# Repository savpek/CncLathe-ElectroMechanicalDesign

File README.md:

CncLathe-ElectroMechanicalDesign
================================

Cnc lathe electro and mechanical design.

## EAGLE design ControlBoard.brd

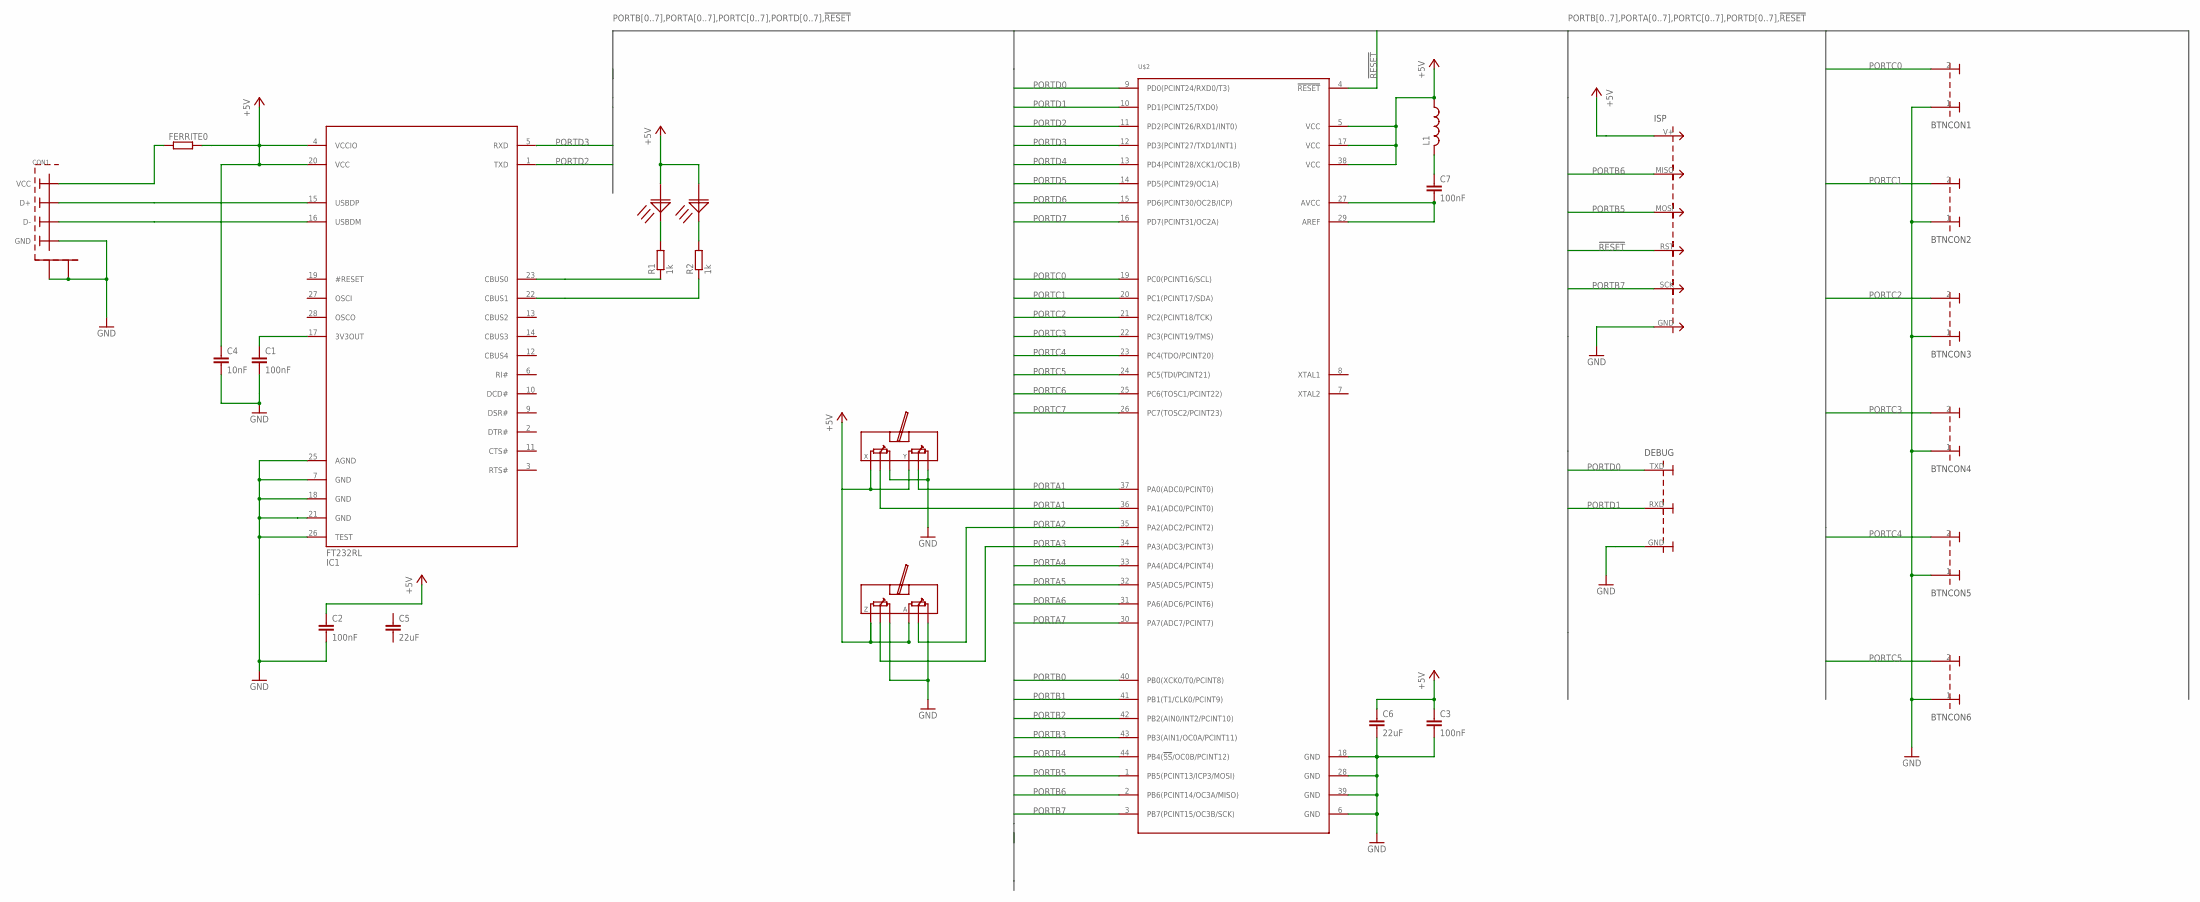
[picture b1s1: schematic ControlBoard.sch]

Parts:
BTNCON1, BTNCON2, BTNCON3, BTNCON4, BTNCON5, BTNCON6: CONNECTOR_2PIN1X2_WIRE; 1X2_WIRE
C1, C2, C3, C7: 100nF; C0805@1; MPN KP-2012SEC
C4: 10nF; C0805@1; MPN 04023D103KAT2A
C5, C6: 22uF; C1206
CON1: USB-BWUERTH-ELECTRONIC-USB-B; USB-B-THROUGH-HOLE
DEBUG: CONNECTOR_3PINUSART; 1X3_USART
FERRITE0: R-EU_R0805; R0805
IC1: FT232RL; SSOP28
ISP: CONNECTOR_6PIN2X3_ISP; 2X3_ISP
JOYSTICK1, JOYSTICK2: JOYSTIC-XYRKJXK122000D; JOYSTICK-RKJXK122000D
L1: L-USL0805; C0805
R1, R2: 1k; R0805
RX: LED; LED_0805
TX: LED; LED_0805
U$2: ATMEGA[164/324/644/644][A/PA]TQFP/QFN/MLF; QFP-44

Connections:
!RESET: ISP.RST, U$2.4 (!RESET)
+5V: C2.1, C3.1, C4.1, C6.1, FERRITE0.2, IC1.4 (VCCIO), IC1.20 (VCC), ISP.V+, JOYSTICK1.X1, JOYSTICK1.Y1, JOYSTICK2.X1, JOYSTICK2.Y1, L1.1, RX.A, TX.A, U$2.5 (VCC), U$2.17 (VCC), U$2.38 (VCC)
GND: BTNCON1.1, BTNCON2.1, BTNCON3.1, BTNCON4.1, BTNCON5.1, BTNCON6.1, C1.2, C2.2, C3.2, C4.2, C6.2, CON1.GND, CON1.SHIELD, CON1.SHIELD@2 (SHIELD), DEBUG.GND, IC1.7 (GND), IC1.18 (GND), IC1.21 (GND), IC1.25 (AGND), IC1.26 (TEST), ISP.GND, JOYSTICK1.X3, JOYSTICK1.Y3, JOYSTICK2.X3, JOYSTICK2.Y3, U$2.6 (GND), U$2.18 (GND), U$2.28 (GND), U$2.39 (GND)
unnamed: C7.2, U$2.27 (AVCC), U$2.29 (AREF)
unnamed: IC1.23 (CBUS0), R1.1
unnamed: IC1.22 (CBUS1), R2.1
unnamed: R1.2, RX.K
unnamed: C7.1, L1.2
unnamed: CON1.D+, IC1.15 (USBDP)
unnamed: CON1.D-, IC1.16 (USBDM)
unnamed: CON1.VCC, FERRITE0.1
unnamed: R2.2, TX.K
unnamed: C1.1, IC1.17 (3V3OUT)
PORTA0: JOYSTICK1.Y2, U$2.37 (PA0(ADC0/PCINT0))
PORTA1: JOYSTICK1.X2, U$2.36 (PA1(ADC0/PCINT0))
PORTA2: JOYSTICK2.Y2, U$2.35 (PA2(ADC2/PCINT2))
PORTA3: JOYSTICK2.X2, U$2.34 (PA3(ADC3/PCINT3))
PORTA4: U$2.33 (PA4(ADC4/PCINT4))
PORTA5: U$2.32 (PA5(ADC5/PCINT5))
PORTA6: U$2.31 (PA6(ADC6/PCINT6))
PORTA7: U$2.30 (PA7(ADC7/PCINT7))
PORTB0: U$2.40 (PB0(XCK0/T0/PCINT8))
PORTB1: U$2.41 (PB1(T1/CLK0/PCINT9))
PORTB2: U$2.42 (PB2(AIN0/INT2/PCINT10))
PORTB3: U$2.43 (PB3(AIN1/OC0A/PCINT11))
PORTB4: U$2.44 (PB4(!SS!/OC0B/PCINT12))
PORTB5: ISP.MOSI, U$2.1 (PB5(PCINT13/ICP3/MOSI))
PORTB6: ISP.MISO, U$2.2 (PB6(PCINT14/OC3A/MISO))
PORTB7: ISP.SCK, U$2.3 (PB7(PCINT15/OC3B/SCK))
PORTC0: BTNCON1.2, U$2.19 (PC0(PCINT16/SCL))
PORTC1: BTNCON2.2, U$2.20 (PC1(PCINT17/SDA))
PORTC2: BTNCON3.2, U$2.21 (PC2(PCINT18/TCK))
PORTC3: BTNCON4.2, U$2.22 (PC3(PCINT19/TMS))
PORTC4: BTNCON5.2, U$2.23 (PC4(TDO/PCINT20))
PORTC5: BTNCON6.2, U$2.24 (PC5(TDI/PCINT21))
PORTC6: U$2.25 (PC6(TOSC1/PCINT22))
PORTC7: U$2.26 (PC7(TOSC2/PCINT23))
PORTD0: DEBUG.TXD, U$2.9 (PD0(PCINT24/RXD0/T3))
PORTD1: DEBUG.RXD, U$2.10 (PD1(PCINT25/TXD0))
PORTD2: IC1.1 (TXD), U$2.11 (PD2(PCINT26/RXD1/INT0))
PORTD3: IC1.5 (RXD), U$2.12 (PD3(PCINT27/TXD1/INT1))
PORTD4: U$2.13 (PD4(PCINT28/XCK1/OC1B))
PORTD5: U$2.14 (PD5(PCINT29/OC1A))
PORTD6: U$2.15 (PD6(PCINT30/OC2B/ICP))
PORTD7: U$2.16 (PD7(PCINT31/OC2A))

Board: 2 copper layers, 26 parts (0 on the bottom side), 30 nets, no tracks yet.

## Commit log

2012-11-12 Added board outlines from mechanical design.
2012-11-18 Added MCU and joystick to schematic.
2012-11-18 Added FT232 and button connectors.
2012-12-02 Added reference for ACD and USB connector.
2012-12-02 Added leds to RXD/TXD->USB
2012-12-16 Layout sketch done.
